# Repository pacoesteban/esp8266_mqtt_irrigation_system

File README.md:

ESP8266 Irrigation system
=========================

A really simple, but probably over-engineered irrigation system using an ESP8266, MQTT and some Perl.

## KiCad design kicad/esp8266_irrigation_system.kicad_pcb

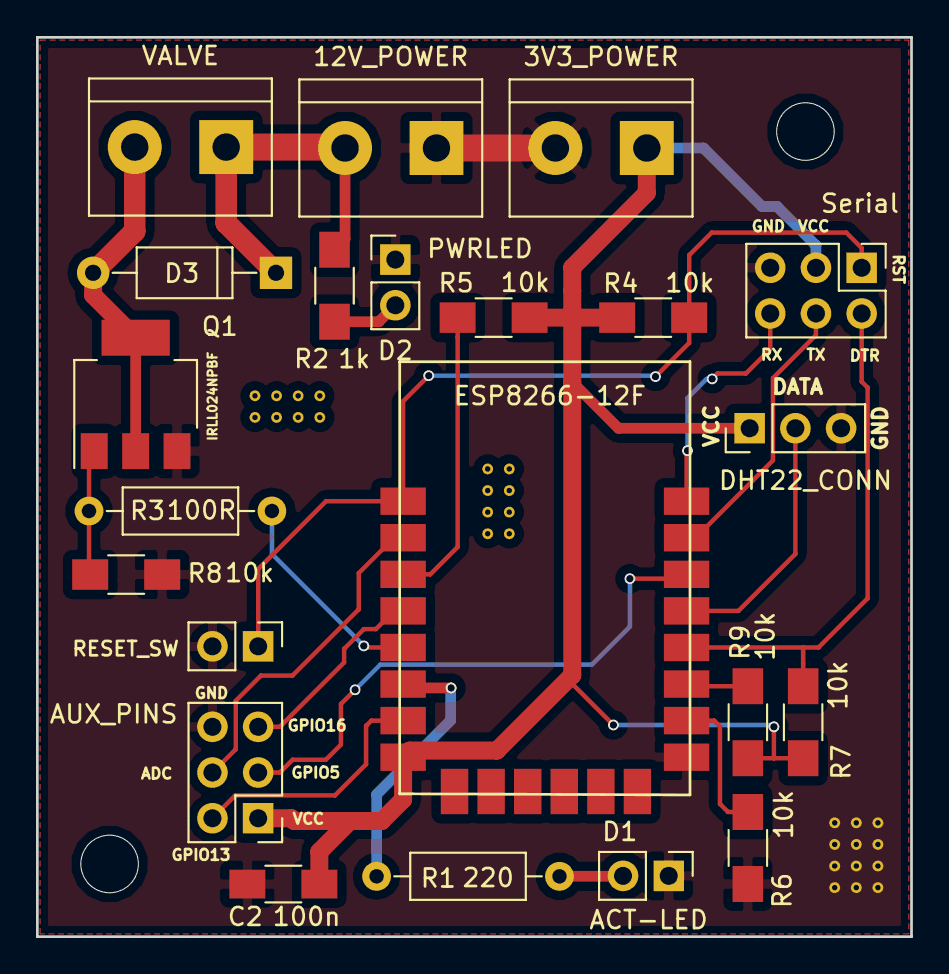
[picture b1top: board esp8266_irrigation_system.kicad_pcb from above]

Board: 2 copper layers, 48.6 x 50.0 mm, 22 parts (0 on the bottom side), 21 nets.

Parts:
C2: 100n; C_1206_HandSoldering
D1: ACT-LED; Pin_Header_Straight_1x02_Pitch2.54mm
D2: PWRLED; Pin_Header_Straight_1x02_Pitch2.54mm
D3: D; D_A-405_P10.16mm_Horizontal
J1: 3V3_POWER; bornier2
J2: AUX_PINS; Pin_Header_Straight_2x03_Pitch2.54mm
L1: VALVE; bornier2
P1: 12V_POWER; bornier2
P2: Serial; Pin_Header_Straight_2x03_Pitch2.54mm
P3: DHT22_CONN; Pin_Header_Straight_1x03_Pitch2.54mm
Q1: IRLL024NPBF; SOT-223-3Lead_TabPin2
R1: 220; R_Axial_DIN0207_L6.3mm_D2.5mm_P10.16mm_Horizontal
R2: 1k; R_1206_HandSoldering
R3: 100R; R_Axial_DIN0207_L6.3mm_D2.5mm_P10.16mm_Horizontal
R4, R5, R6, R7, R8, R9: 10k; R_1206_HandSoldering
SW1: RESET_SW; Pin_Header_Straight_1x02_Pitch2.54mm
U2: ESP8266-12F

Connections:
3.3V: C2.1, J1.1, J2.1, P2.3, P3.1, R4.2, R5.2, R7.1, R9.1, U2.8
12V: D3.1, L1.1, P1.2, R2.2
ADC: J2.4, U2.2
DHT22: P3.2, U2.19
DTR: P2.2, R7.2, U2.18
GND: C2.2, D1.1, D2.1, J1.2, J2.6, P1.1, P2.5, P3.3, Q1.3, R6.1, R8.2, SW1.2, U2.15
GPIO5: J2.3, U2.20
GPIO13: J2.2, U2.7
GPIO16: J2.5, U2.4
INFO_LED: R1.2, U2.6
unnamed: D1.2, R1.1
unnamed: D2.2, R2.1
unnamed: D3.2, L1.2, Q1.2
unnamed: Q1.1, R3.1, R8.1
unnamed: R5.1, U2.3
unnamed: R6.2, U2.16
unnamed: R9.2, U2.17
RST: P2.1, R4.1, SW1.1, U2.1
RX: P2.6, U2.22
TX: P2.4, U2.21
WATER_VALVE: R3.2, U2.5

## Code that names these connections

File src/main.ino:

#include <ESPHelper.h>
#include <DHT.h>
#include <myNetworks.h>

#define INFO_LED 12
#define WATER_VALVE 14
#define DHTPIN 4
#define DHTTYPE DHT22
#define GPIO_PIN 13

#define DEBUG 0
#define CHECK_INTERVAL 300000

netInfo homeNet = {.mqttHost = MQTT_BROKER,
                   .mqttUser = "",
                   .mqttPass = "",
                   .mqttPort = 1883,
                   .ssid = WIFI_SSID,
                   .pass = WIFI_PASSWD
                  };

ESPHelper myESP( &homeNet );
DHT dht( DHTPIN, DHTTYPE );

// Connect to the WiFi
float temperature = 0;
int humidity = 0;
float moisture = 0.0;
int onTime = 0;
const char *irr01Topic = "/sensors/irr01";
const char *sensorsTopic = "/sensors/info";
unsigned long currentMillis = 0;
unsigned long previousMillis = 0;

void callback( char *topic, byte *payload, unsigned int length )
{
    yield();

    if ( payload[0] == '#' && payload[3] == '#' ) {
        yield();
        onTime = ( payload[1] - '0' ) * 10;
        onTime += ( payload[2] - '0' );
        yield();

        if ( onTime > 0 ) {
            irrigate( onTime * 60 );
        }
    }

    Serial.println();
}

void collectData()
{
    bool dht_ok = false;
    int readCount = 5;
    moisture = 0;
    yield();

    while ( !dht_ok && readCount > 0 ) {
        temperature = dht.readTemperature();
        yield();
        humidity = dht.readHumidity();
        readCount--;

        if ( isnan( temperature ) || isnan( humidity ) ) {
            delay( 1000 );
        } else {
            dht_ok = true;
        }
    }

    yield();

    if ( isnan( temperature ) || isnan( humidity ) ) {
        temperature = 0;
        humidity = 0;
    }

    if ( DEBUG ) {
        Serial.println( humidity );
        Serial.println( moisture );
        Serial.println( temperature );
    }
}

void sendData()
{
    char message[27];
    char char_t[7];
    dtostrf( temperature, 5, 2, char_t );
    yield();
    sprintf( message, "SR01-IRR1|%s|%i|%i|%i",
             char_t, humidity, ( int )moisture, onTime );
    yield();

    if ( DEBUG ) {
        Serial.print( "Sending data: " );
        Serial.println( message );
    }

    yield();
    myESP.publish( sensorsTopic, message );
}

void irrigate( int seconds )
{
    char message[16];
    yield();

    if ( DEBUG ) {
        Serial.print( "Regant: " );
        Serial.println( seconds );
    }

    digitalWrite( INFO_LED, HIGH );
    digitalWrite( WATER_VALVE, HIGH );

    while ( seconds > 0 ) {
        delay( 1000 );
        seconds--;
    }

    digitalWrite( WATER_VALVE, LOW );
    digitalWrite( INFO_LED, LOW );
}

void setup()
{
    yield();
    Serial.begin( 115200 );
    delay( 10 );
    myESP.OTA_enable();
    myESP.OTA_setPassword( OTA_PASSWD );
    myESP.OTA_setHostnameWithVersion( "IRR01" );
    myESP.addSubscription( irr01Topic );
    myESP.begin();
    myESP.setCallback(
        callback ); //can only set callback after begin method. Calling before begin() will not set the callback (return false)
    yield();
    pinMode( INFO_LED, OUTPUT );
    pinMode( WATER_VALVE, OUTPUT );
    pinMode( GPIO_PIN, INPUT );
    delay( 5 );
    // reset, just in case.
    yield();
    digitalWrite( WATER_VALVE, LOW );
    yield();
    digitalWrite( INFO_LED, LOW );
    delay( 5 );
    dht.begin();
    delay( 5 );
    // We start by connecting to a WiFi network
    Serial.println();
    Serial.println();
    Serial.print( "Connecting to " );
    Serial.println( homeNet.ssid );
    delay( 5000 );
    Serial.println( "IP address: " );
    Serial.println( myESP.getIP() );
    delay( 250 );

    // flash to indicate boot process.
    for ( int i = 0; i < 3; i++ ) {
        digitalWrite( INFO_LED, HIGH );
        delay( 200 );
        digitalWrite( INFO_LED, LOW );
        delay( 200 );
    }

    yield();
}

void loop()
{
    yield();
    myESP.loop();
    currentMillis = millis();

    if ( ( unsigned long )( currentMillis - previousMillis ) > CHECK_INTERVAL ) {
        previousMillis = currentMillis;
        collectData();
        sendData();
        onTime = 0;
    }
}

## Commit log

2017-05-27 working version
2017-06-21 trying not to block on dht readings
2017-06-21 masking personal data to publish more easily
2017-06-22 board re-done for fabrication
2017-10-06 new board design
2017-11-05 change to use ESPHelper, enabled OTA and removing unused fetures
